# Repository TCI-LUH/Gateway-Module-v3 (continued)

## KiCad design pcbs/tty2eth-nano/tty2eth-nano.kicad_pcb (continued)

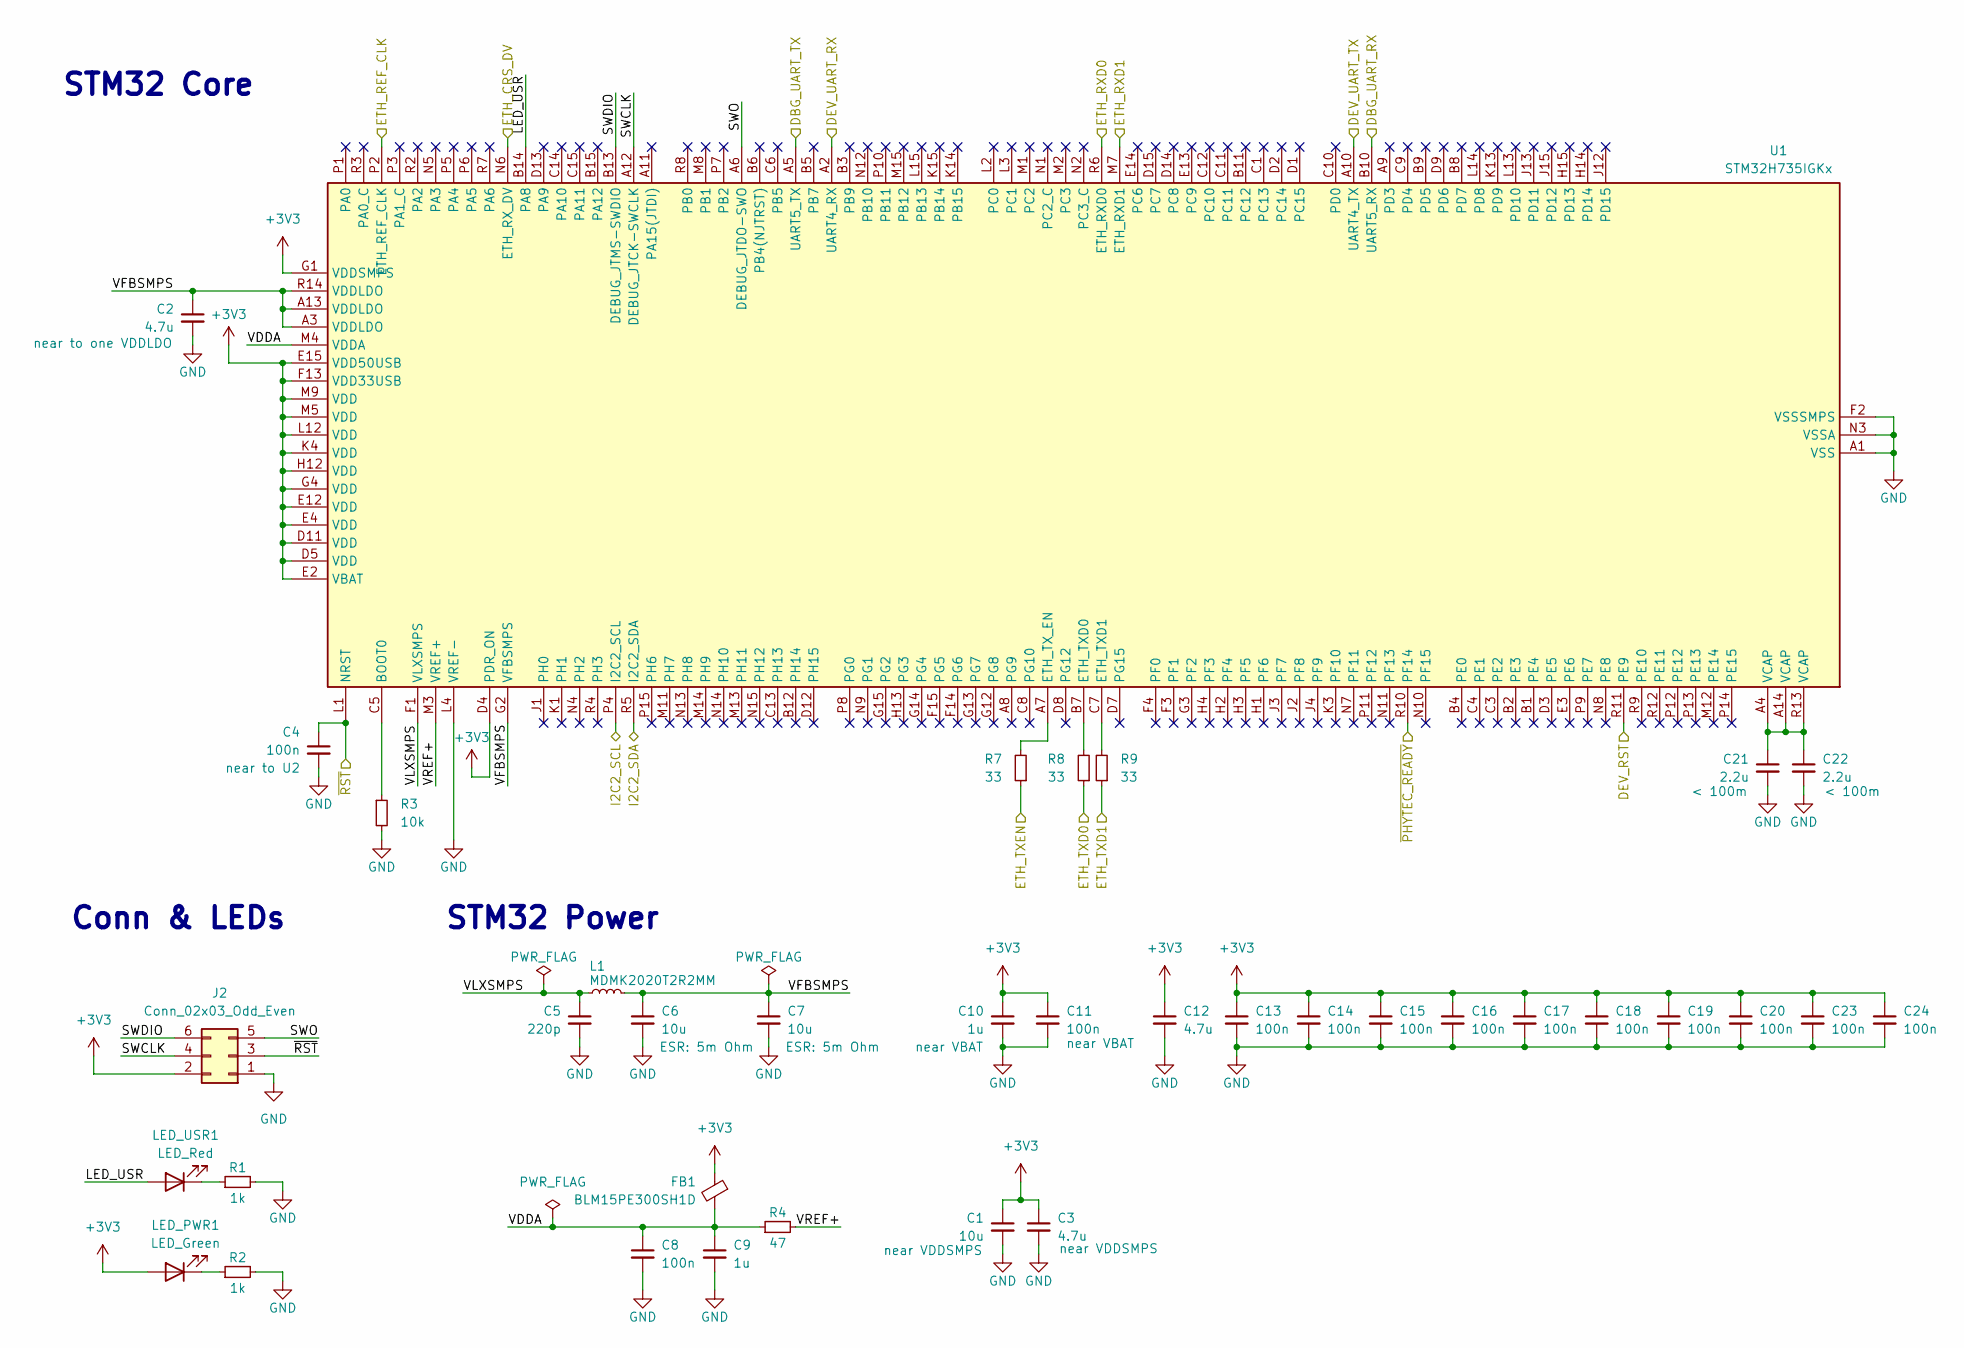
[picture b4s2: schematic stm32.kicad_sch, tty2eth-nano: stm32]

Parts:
C1, C6, C7: 10u; C_0402; Mouser Part Number 187-CL05A106MP6NUN8
C2, C3, C12: 4.7u; C_0402; Mouser Part Number 187-CL05A475MP5NRNC
C4, C8, C11, C13, C14, C15, C16, C17, C18, C19, C20, C23, C24: 100n; C_0402; Mouser Part Number 80-C0402C104K4R7867
C5: 220p; C_0402; Mouser Part Number 187-CL05C221JB5NNNC
C9, C10: 1u; C_0402; Mouser Part Number 187-CL05A105KO5NNNC
C21, C22: 2.2u; C_0402; Mouser Part Number 963-MSASL105SB5225KF
FB1: BLM15PE300SH1D; L_0402; Mouser Part Number 81-BLM15PE300SH1D
J2: Conn_02x03_Odd_Even; SAMTEC_CLT-103-01-F-D; Mouser Part Number 710-62000621121
L1: MDMK2020T2R2MM; L_Taiyo-Yuden_NR-20xx; Mouser Part Number 963-MDMK2020T2R2MM
LED_PWR1: LED_Green; LED_0402_1005Metric_Pad0.77x0.64mm_HandSolder; Mouser Part Number 755-SML-P11MTT86R
LED_USR1: LED_Red; LED_0402_1005Metric_Pad0.77x0.64mm_HandSolder; Mouser Part Number 755-SML-P11UTT86R
R1, R2: 1k; R_0402; Mouser Part Number 652-CR0402AFX1001GLF
R3: 10k; R_0402; Mouser Part Number 652-CR0402AFX1002GAS
R4: 47; R_0402; Mouser Part Number 652-CR0402FX-47R0GLF
R7, R8, R9: 33; R_0402; Mouser Part Number 652-CR0402FX-47R0GLF
U1: STM32H735IGKx; UFBGA-201_10x10mm_Layout15x15_P0.65mm; Mouser Part Number 511-STM32H735IGK6

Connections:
+3V3: C1.1, C3.1, C10.1, C11.1, C12.1, C13.1, C14.1, C15.1, C16.1, C17.1, C18.1, C19.1, C20.1, C23.1, C24.1, FB1.1, J2.2, LED_PWR1.2 (A), U1.D4 (PDR_ON), U1.D5 (VDD), U1.D11 (VDD), U1.E2 (VBAT), U1.E4 (VDD), U1.E12 (VDD), U1.E15 (VDD50USB), U1.F13 (VDD33USB), U1.G1 (VDDSMPS), U1.G4 (VDD), U1.H12 (VDD), U1.K4 (VDD), U1.L12 (VDD), U1.M5 (VDD), U1.M9 (VDD); also elsewhere on the board
/DBG_UART_RX: U1.B10 (UART5_RX); also elsewhere on the board
/DBG_UART_TX: U1.A5 (UART5_TX); also elsewhere on the board
/DEV_RST: U1.R11 (PE9); also elsewhere on the board
/DEV_UART_RX: U1.A2 (UART4_RX); also elsewhere on the board
/DEV_UART_TX: U1.A10 (UART4_TX); also elsewhere on the board
/ETH_CRS_DV: U1.N6 (ETH_RX_DV); also elsewhere on the board
/ETH_REF_CLK: U1.P2 (ETH_REF_CLK); also elsewhere on the board
/ETH_RXD0: U1.R6 (ETH_RXD0); also elsewhere on the board
/ETH_RXD1: U1.M7 (ETH_RXD1); also elsewhere on the board
/ETH_TXD0: R8.1; also elsewhere on the board
/ETH_TXD1: R9.1; also elsewhere on the board
/ETH_TXEN: R7.1; also elsewhere on the board
/SCL: U1.P4 (I2C2_SCL); also elsewhere on the board
/SDA: U1.R5 (I2C2_SDA); also elsewhere on the board
/stm32/LED_USR: LED_USR1.2 (A), U1.B14 (PA8)
/stm32/SWCLK: J2.4, U1.A12 (DEBUG_JTCK-SWCLK)
/stm32/SWDIO: J2.6, U1.B13 (DEBUG_JTMS-SWDIO)
/stm32/SWO: J2.5, U1.A6 (DEBUG_JTDO-SWO)
/stm32/VDDA: C8.1, C9.1, FB1.2, R4.1, U1.M4 (VDDA)
/stm32/VFBSMPS: C2.1, C6.1, C7.1, L1.1, U1.A3 (VDDLDO), U1.A13 (VDDLDO), U1.G2 (VFBSMPS), U1.R14 (VDDLDO)
/stm32/VLXSMPS: C5.1, L1.2, U1.F1 (VLXSMPS)
/stm32/VREF+: R4.2, U1.M3 (VREF+)
/~PHYTEC_READY: U1.R10 (PF14); also elsewhere on the board
/~RST: C4.1, J2.3, U1.L1 (NRST); also elsewhere on the board
GND: C1.2, C2.2, C3.2, C4.2, C5.2, C6.2, C7.2, C8.2, C9.2, C10.2, C11.2, C12.2, C13.2, C14.2, C15.2, C16.2, C17.2, C18.2, C19.2, C20.2, C21.2, C22.2, C23.2, C24.2, J2.1, R1.2, R2.2, R3.2, U1.A1 (VSS), U1.A15 (VSS), U1.C2 (VSS), U1.D6 (VSS), U1.D10 (VSS), U1.E1 (VSS), U1.F2 (VSSSMPS), U1.F6 (VSS), U1.F7 (VSS), U1.F8 (VSS), U1.F9 (VSS), U1.F10 (VSS), U1.F12 (VSS), U1.G6 (VSS), U1.G7 (VSS), U1.G8 (VSS), U1.G9 (VSS), U1.G10 (VSS), U1.H6 (VSS), U1.H7 (VSS), U1.H8 (VSS), U1.H9 (VSS), U1.H10 (VSS), U1.J6 (VSS), U1.J7 (VSS), U1.J8 (VSS), U1.J9 (VSS), U1.J10 (VSS), U1.J14 (VSS), U1.K2 (VSS), U1.K6 (VSS), U1.K7 (VSS), U1.K8 (VSS), U1.K9 (VSS), U1.K10 (VSS), U1.K12 (VSS), U1.L4 (VREF-), U1.M6 (VSS), U1.M10 (VSS), U1.N3 (VSSA), U1.R1 (VSS), U1.R15 (VSS); also elsewhere on the board
unnamed: C21.1, C22.1, U1.A4 (VCAP), U1.A14 (VCAP), U1.R13 (VCAP)
unnamed: LED_PWR1.1 (K), R2.1
unnamed: LED_USR1.1 (K), R1.1
unnamed: R3.1, U1.C5 (BOOT0)
unnamed: R7.2, U1.A7 (ETH_TX_EN)
unnamed: R8.2, U1.B7 (ETH_TXD0)
unnamed: R9.2, U1.C7 (ETH_TXD1)

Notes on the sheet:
STM32 Power
STM32 Core
Conn & LEDs

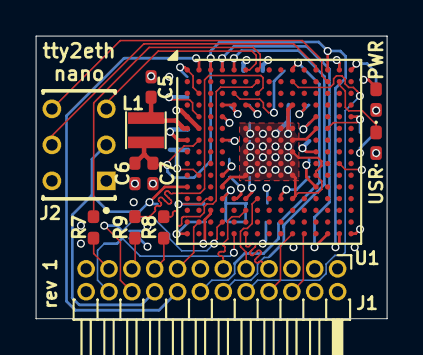
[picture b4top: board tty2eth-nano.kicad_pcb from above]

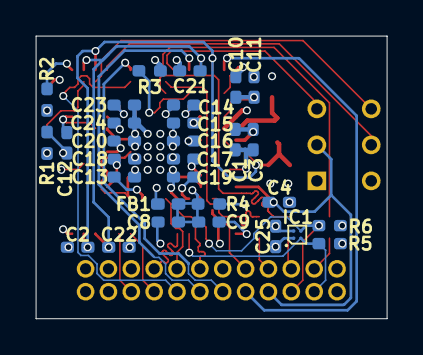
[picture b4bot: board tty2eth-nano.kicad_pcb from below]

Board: 4 copper layers, 19.5 x 15.7 mm, 42 parts (30 on the bottom side), 33 nets.

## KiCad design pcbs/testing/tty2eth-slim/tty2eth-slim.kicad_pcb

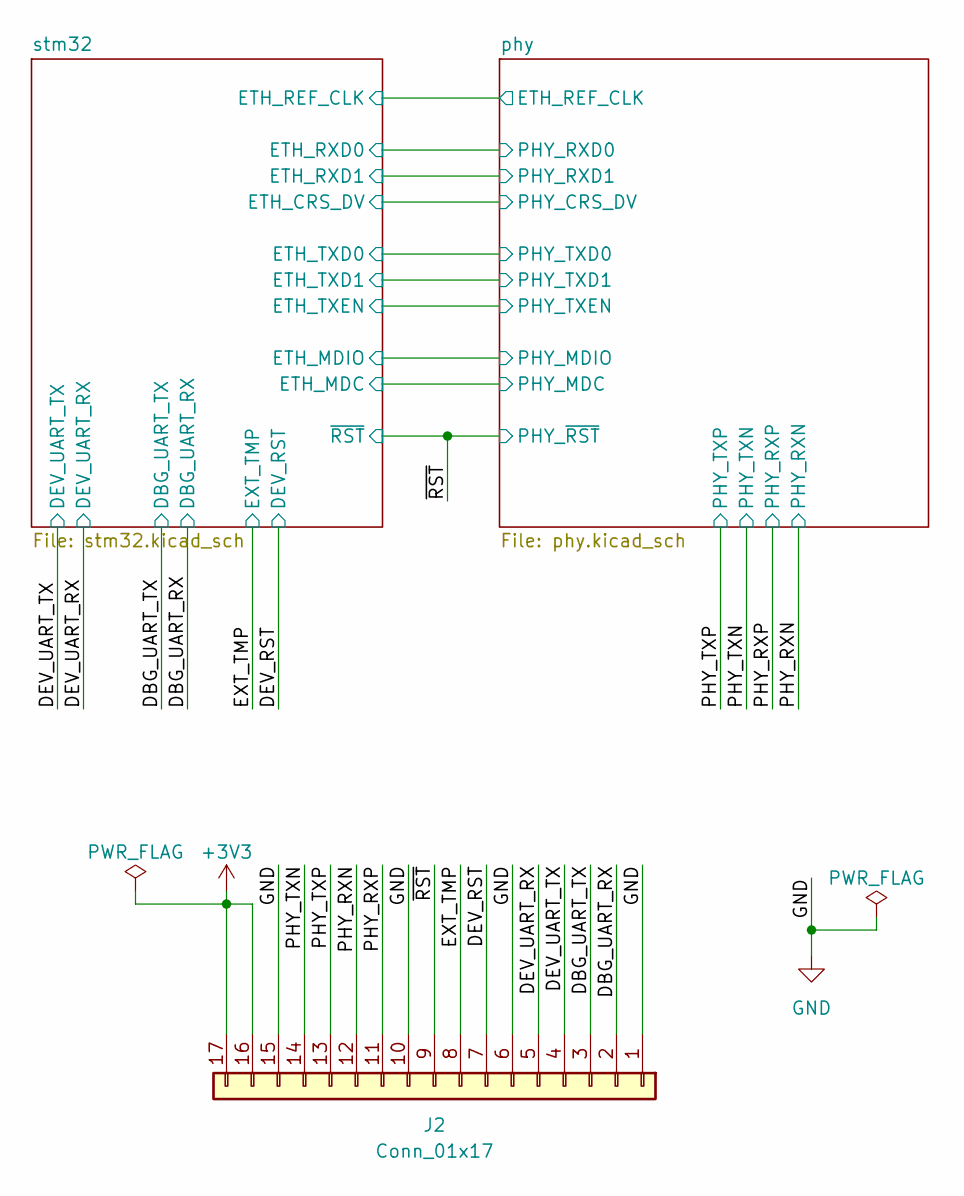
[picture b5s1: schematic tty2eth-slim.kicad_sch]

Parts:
J2: Conn_01x17; PinHeader_1x17_P1.27mm_Horizontal; Mouser Part Number 855-M50-3932042

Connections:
+3V3: J2.16, J2.17; also elsewhere on the board
/DBG_UART_RX: J2.2; also elsewhere on the board
/DBG_UART_TX: J2.3; also elsewhere on the board
/DEV_RST: J2.7; also elsewhere on the board
/DEV_UART_RX: J2.5; also elsewhere on the board
/DEV_UART_TX: J2.4; also elsewhere on the board
/EXT_TMP: J2.8; also elsewhere on the board
/PHY_RXN: J2.12; also elsewhere on the board
/PHY_RXP: J2.11; also elsewhere on the board
/PHY_TXN: J2.14; also elsewhere on the board
/PHY_TXP: J2.13; also elsewhere on the board
/~RST: J2.9; also elsewhere on the board
GND: J2.1, J2.6, J2.10, J2.15; also elsewhere on the board

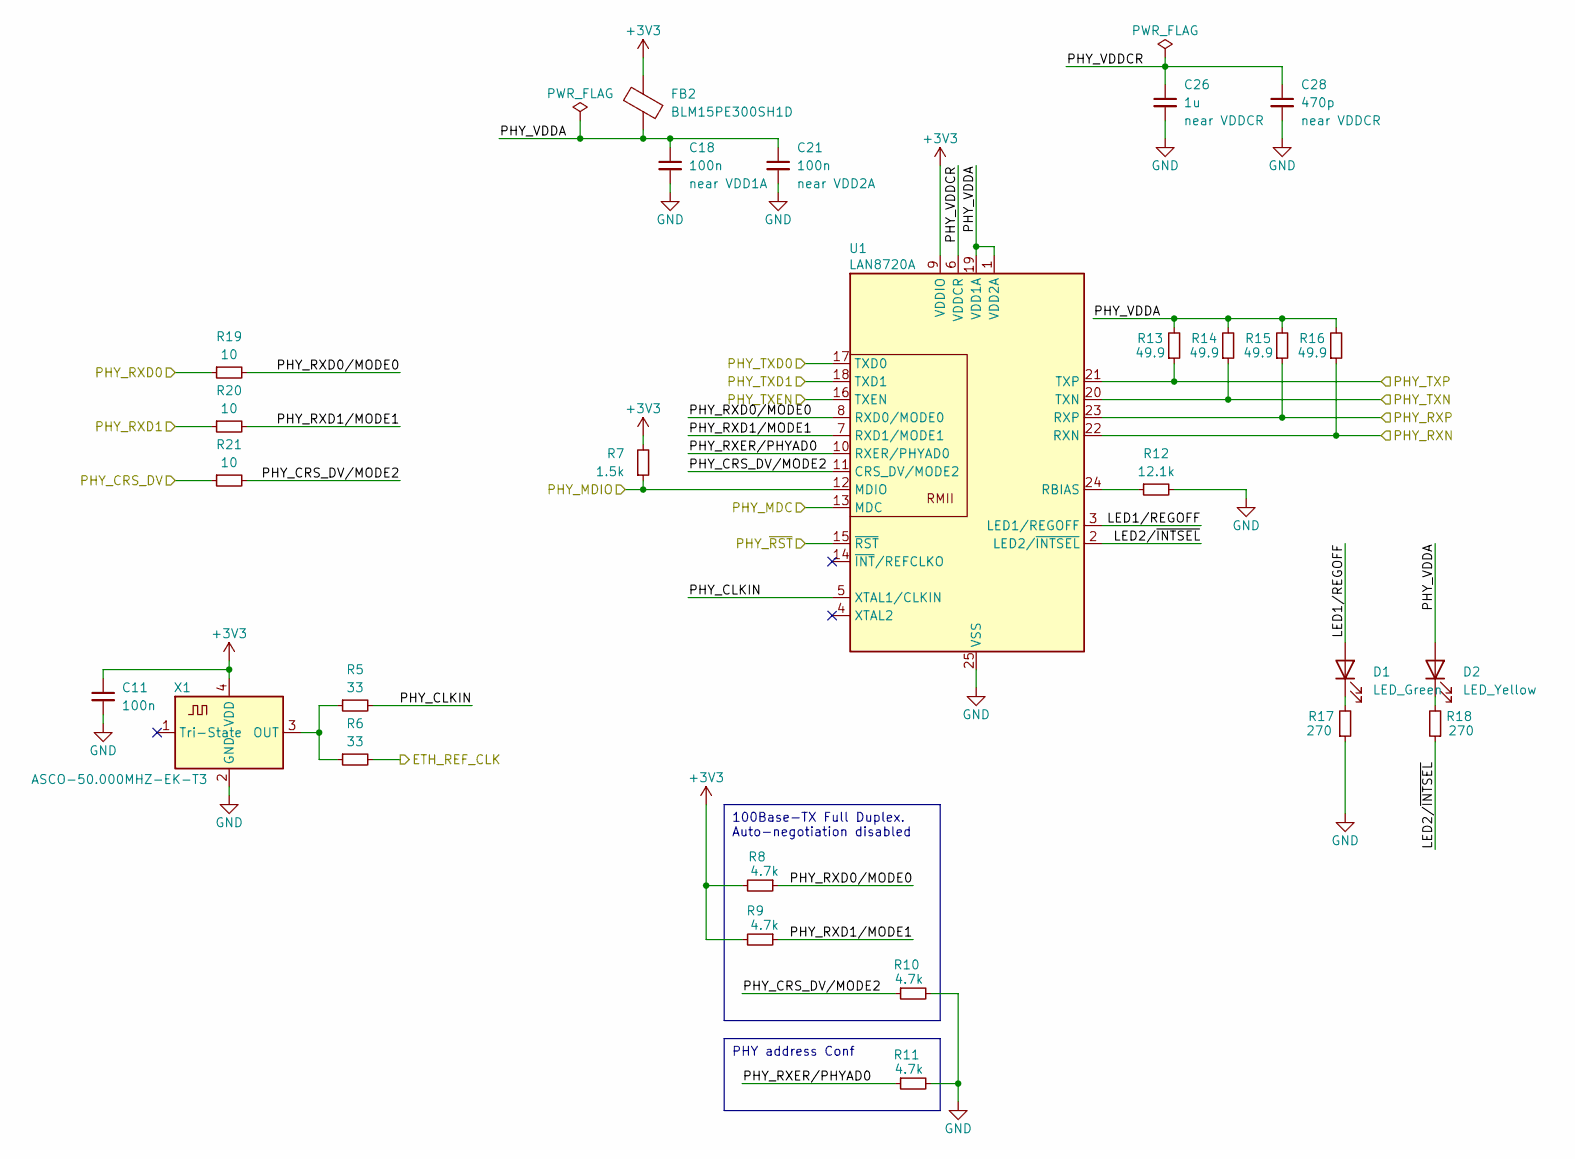
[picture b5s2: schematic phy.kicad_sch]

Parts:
C11, C18, C21: 100n; C_0402_1005Metric_Pad0.74x0.62mm_HandSolder; Mouser Part Number 187-80-C0402C104K4R7867
C26: 1u; C_0402_1005Metric_Pad0.74x0.62mm_HandSolder; Mouser Part Number 187-CL05A105KO5NNNC
C28: 470p; C_0402_1005Metric_Pad0.74x0.62mm_HandSolder; Mouser Part Number 187-CL05C471JB5NNWC
D1: LED_Green; LED_0402_1005Metric_Pad0.77x0.64mm_HandSolder; Mouser Part Number 755-SML-P11MTT86R
D2: LED_Yellow; LED_0402_1005Metric_Pad0.77x0.64mm_HandSolder; Mouser Part Number 755-SML-P11YTT86R
FB2: BLM15PE300SH1D; L_0402_1005Metric_Pad0.77x0.64mm_HandSolder; Mouser Part Number 81-BLM15PE300SH1D
R5, R6: 33; R_0402_1005Metric_Pad0.72x0.64mm_HandSolder; Mouser Part Number 652-CR0402FX-33R0GLF
R7: 1.5k; R_0402_1005Metric_Pad0.72x0.64mm_HandSolder; Mouser Part Number 652-CR0402FX-1501GLF
R8, R9, R10, R11: 4.7k; R_0402_1005Metric_Pad0.72x0.64mm_HandSolder; Mouser Part Number 652-CR0402FX-4701GLF
R12: 12.1k; R_0402_1005Metric_Pad0.72x0.64mm_HandSolder; Mouser Part Number 652-CR0402-FX1212GLF
R13, R14, R15, R16: 49.9; R_0402_1005Metric_Pad0.72x0.64mm_HandSolder; Mouser Part Number 652-CR0402FX-49R9GLF
R17, R18: 270; R_0402_1005Metric_Pad0.72x0.64mm_HandSolder; Mouser Part Number 652-CR0402FX-2700GLF
R19, R20, R21: 10; R_0402_1005Metric_Pad0.72x0.64mm_HandSolder; Mouser Part Number 652-CR0402FX-10R0GLF
U1: LAN8720A; VQFN-24-1EP_4x4mm_P0.5mm_EP2.5x2.5mm_ThermalVias; Mouser Part Number 579-LAN8720ACPTRABC
X1: ASCO-50.000MHZ-EK-T3; Oscillator_SMD_Abracon_ASCO-4Pin_1.6x1.2mm; Mouser Part Number 815-ASCO-50-EK-T3

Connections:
+3V3: C11.1, FB2.2, R7.2, R8.2, R9.2, U1.9 (VDDIO), X1.4 (VDD); also elsewhere on the board
/PHY_RXN: R16.1, U1.22 (RXN); also elsewhere on the board
/PHY_RXP: R15.1, U1.23 (RXP); also elsewhere on the board
/PHY_TXN: R14.1, U1.20 (TXN); also elsewhere on the board
/PHY_TXP: R13.1, U1.21 (TXP); also elsewhere on the board
/phy/ETH_REF_CLK: R6.2; also elsewhere on the board
/phy/LED1/REGOFF: D1.2 (A), U1.3 (LED1/REGOFF)
/phy/LED2/~INTSEL: R18.1, U1.2 (LED2/~INTSEL)
/phy/PHY_CLKIN: R5.2, U1.5 (XTAL1/CLKIN)
/phy/PHY_CRS_DV: R21.1; also elsewhere on the board
/phy/PHY_CRS_DV/MODE2: R10.1, R21.2, U1.11 (CRS_DV/MODE2)
/phy/PHY_MDC: U1.13 (MDC); also elsewhere on the board
/phy/PHY_MDIO: R7.1, U1.12 (MDIO); also elsewhere on the board
/phy/PHY_RXD0: R19.1; also elsewhere on the board
/phy/PHY_RXD0/MODE0: R8.1, R19.2, U1.8 (RXD0/MODE0)
/phy/PHY_RXD1: R20.1; also elsewhere on the board
/phy/PHY_RXD1/MODE1: R9.1, R20.2, U1.7 (RXD1/MODE1)
/phy/PHY_RXER/PHYAD0: R11.1, U1.10 (RXER/PHYAD0)
/phy/PHY_TXD0: U1.17 (TXD0); also elsewhere on the board
/phy/PHY_TXD1: U1.18 (TXD1); also elsewhere on the board
/phy/PHY_TXEN: U1.16 (TXEN); also elsewhere on the board
/phy/PHY_VDDA: C18.1, C21.1, D2.2 (A), FB2.1, R13.2, R14.2, R15.2, R16.2, U1.1 (VDD2A), U1.19 (VDD1A)
/phy/PHY_VDDCR: C26.1, C28.1, U1.6 (VDDCR)
/~RST: U1.15 (~RST); also elsewhere on the board
GND: C11.2, C18.2, C21.2, C26.2, C28.2, R10.2, R11.2, R12.2, R17.1, U1.25 (VSS), X1.2 (GND); also elsewhere on the board
unnamed: D1.1 (K), R17.2
unnamed: D2.1 (K), R18.2
unnamed: R12.1, U1.24 (RBIAS)
unnamed: R5.1, R6.1, X1.3 (OUT)

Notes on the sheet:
PHY address Conf
100Base-TX Full Duplex. Auto-negotiation disabled

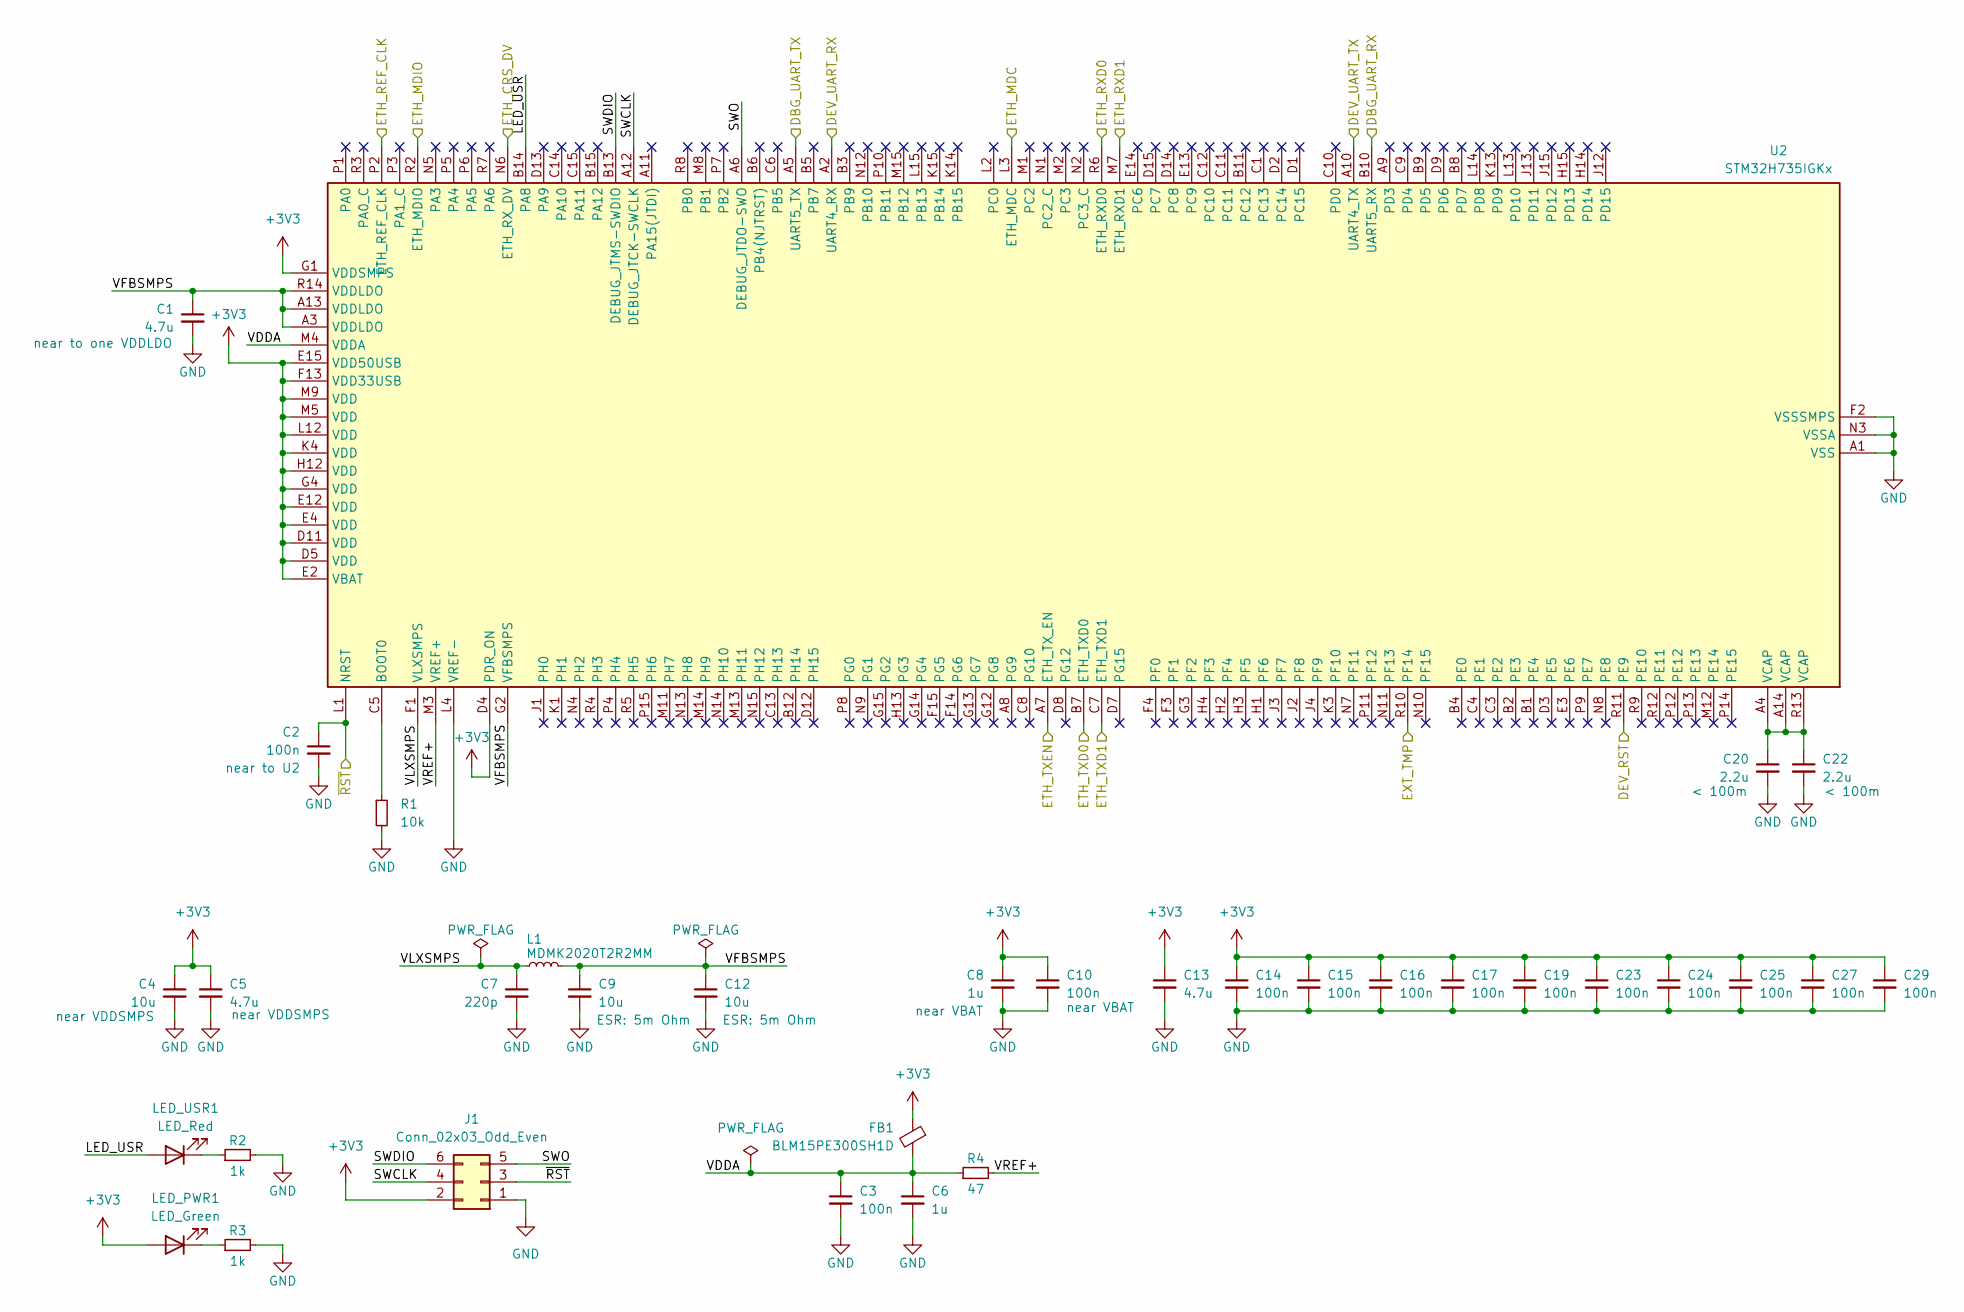
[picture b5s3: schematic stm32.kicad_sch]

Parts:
C1, C5, C13: 4.7u; C_0402_1005Metric_Pad0.74x0.62mm_HandSolder; Mouser Part Number 187-CL05A475MP5NRNC
C2, C3, C10, C14, C15, C16, C17, C19, C23, C24, C25, C27, C29: 100n; C_0402_1005Metric_Pad0.74x0.62mm_HandSolder; Mouser Part Number 187-80-C0402C104K4R7867
C4, C9, C12: 10u; C_0402_1005Metric_Pad0.74x0.62mm_HandSolder; Mouser Part Number 187-CL05A106MP6NUN8
C6, C8: 1u; C_0402_1005Metric_Pad0.74x0.62mm_HandSolder; Mouser Part Number 187-CL05A105KO5NNNC
C7: 220p; C_0402_1005Metric_Pad0.74x0.62mm_HandSolder; Mouser Part Number 187-CL05C221JB5NNNC
C20, C22: 2.2u; C_0402_1005Metric_Pad0.74x0.62mm_HandSolder; Mouser Part Number 963-MSASL105SB5225KF
FB1: BLM15PE300SH1D; L_0402_1005Metric_Pad0.77x0.64mm_HandSolder; Mouser Part Number 81-BLM15PE300SH1D
J1: Conn_02x03_Odd_Even; SAMTEC_CLT-103-01-F-D; Mouser Part Number 710-62000621121
L1: MDMK2020T2R2MM; L_Taiyo-Yuden_NR-20xx; Mouser Part Number 963-MDMK2020T2R2MM
LED_PWR1: LED_Green; LED_0402_1005Metric_Pad0.77x0.64mm_HandSolder; Mouser Part Number 755-SML-P11MTT86R
LED_USR1: LED_Red; LED_0402_1005Metric_Pad0.77x0.64mm_HandSolder; Mouser Part Number 755-SML-P11UTT86R
R1: 10k; R_0402_1005Metric_Pad0.72x0.64mm_HandSolder; Mouser Part Number 652-CR0402AFX1002GAS
R2, R3: 1k; R_0402_1005Metric_Pad0.72x0.64mm_HandSolder; Mouser Part Number 652-CR0402AFX1001GLF
R4: 47; R_0402_1005Metric_Pad0.72x0.64mm_HandSolder; Mouser Part Number 652-CR0402FX-47R0GLF
U2: STM32H735IGKx; UFBGA-201_10x10mm_Layout15x15_P0.65mm; Mouser Part Number 511-STM32H735IGK6

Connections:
+3V3: C4.1, C5.1, C8.1, C10.1, C13.1, C14.1, C15.1, C16.1, C17.1, C19.1, C23.1, C24.1, C25.1, C27.1, C29.1, FB1.1, J1.2, LED_PWR1.2 (A), U2.D4 (PDR_ON), U2.D5 (VDD), U2.D11 (VDD), U2.E2 (VBAT), U2.E4 (VDD), U2.E12 (VDD), U2.E15 (VDD50USB), U2.F13 (VDD33USB), U2.G1 (VDDSMPS), U2.G4 (VDD), U2.H12 (VDD), U2.K4 (VDD), U2.L12 (VDD), U2.M5 (VDD), U2.M9 (VDD); also elsewhere on the board
/DBG_UART_RX: U2.B10 (UART5_RX); also elsewhere on the board
/DBG_UART_TX: U2.A5 (UART5_TX); also elsewhere on the board
/DEV_RST: U2.R11 (PE9); also elsewhere on the board
/DEV_UART_RX: U2.A2 (UART4_RX); also elsewhere on the board
/DEV_UART_TX: U2.A10 (UART4_TX); also elsewhere on the board
/EXT_TMP: U2.R10 (PF14); also elsewhere on the board
/phy/ETH_REF_CLK: U2.P2 (ETH_REF_CLK); also elsewhere on the board
/phy/PHY_CRS_DV: U2.N6 (ETH_RX_DV); also elsewhere on the board
/phy/PHY_MDC: U2.L3 (PC1); also elsewhere on the board
/phy/PHY_MDIO: U2.R2 (ETH_MDIO); also elsewhere on the board
/phy/PHY_RXD0: U2.R6 (ETH_RXD0); also elsewhere on the board
/phy/PHY_RXD1: U2.M7 (ETH_RXD1); also elsewhere on the board
/phy/PHY_TXD0: U2.B7 (ETH_TXD0); also elsewhere on the board
/phy/PHY_TXD1: U2.C7 (ETH_TXD1); also elsewhere on the board
/phy/PHY_TXEN: U2.A7 (ETH_TX_EN); also elsewhere on the board
/stm32/LED_USR: LED_USR1.2 (A), U2.B14 (PA8)
/stm32/SWCLK: J1.4, U2.A12 (DEBUG_JTCK-SWCLK)
/stm32/SWDIO: J1.6, U2.B13 (DEBUG_JTMS-SWDIO)
/stm32/SWO: J1.5, U2.A6 (DEBUG_JTDO-SWO)
/stm32/VDDA: C3.1, C6.1, FB1.2, R4.1, U2.M4 (VDDA)
/stm32/VFBSMPS: C1.1, C9.1, C12.1, L1.1, U2.A3 (VDDLDO), U2.A13 (VDDLDO), U2.G2 (VFBSMPS), U2.R14 (VDDLDO)
/stm32/VLXSMPS: C7.1, L1.2, U2.F1 (VLXSMPS)
/stm32/VREF+: R4.2, U2.M3 (VREF+)
/~RST: C2.1, J1.3, U2.L1 (NRST); also elsewhere on the board
GND: C1.2, C2.2, C3.2, C4.2, C5.2, C6.2, C7.2, C8.2, C9.2, C10.2, C12.2, C13.2, C14.2, C15.2, C16.2, C17.2, C19.2, C20.2, C22.2, C23.2, C24.2, C25.2, C27.2, C29.2, J1.1, R1.2, R2.2, R3.2, U2.A1 (VSS), U2.A15 (VSS), U2.C2 (VSS), U2.D6 (VSS), U2.D10 (VSS), U2.E1 (VSS), U2.F2 (VSSSMPS), U2.F6 (VSS), U2.F7 (VSS), U2.F8 (VSS), U2.F9 (VSS), U2.F10 (VSS), U2.F12 (VSS), U2.G6 (VSS), U2.G7 (VSS), U2.G8 (VSS), U2.G9 (VSS), U2.G10 (VSS), U2.H6 (VSS), U2.H7 (VSS), U2.H8 (VSS), U2.H9 (VSS), U2.H10 (VSS), U2.J6 (VSS), U2.J7 (VSS), U2.J8 (VSS), U2.J9 (VSS), U2.J10 (VSS), U2.J14 (VSS), U2.K2 (VSS), U2.K6 (VSS), U2.K7 (VSS), U2.K8 (VSS), U2.K9 (VSS), U2.K10 (VSS), U2.K12 (VSS), U2.L4 (VREF-), U2.M6 (VSS), U2.M10 (VSS), U2.N3 (VSSA), U2.R1 (VSS), U2.R15 (VSS); also elsewhere on the board
unnamed: C20.1, C22.1, U2.A4 (VCAP), U2.A14 (VCAP), U2.R13 (VCAP)
unnamed: LED_PWR1.1 (K), R3.1
unnamed: LED_USR1.1 (K), R2.1
unnamed: R1.1, U2.C5 (BOOT0)

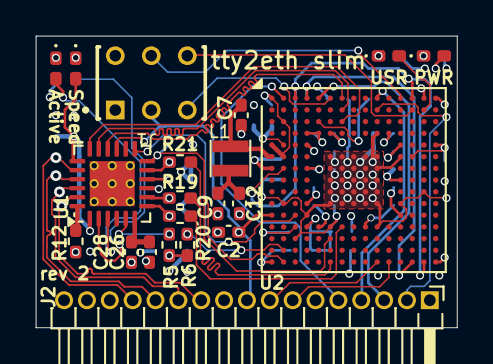
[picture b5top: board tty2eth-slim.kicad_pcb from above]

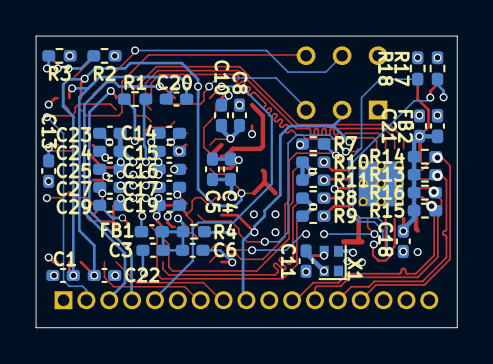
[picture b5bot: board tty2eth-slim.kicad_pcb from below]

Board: 4 copper layers, 23.4 x 16.2 mm, 62 parts (41 on the bottom side), 47 nets.
